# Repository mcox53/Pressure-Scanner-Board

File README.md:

# Pressure-Scanner-Board

Fab To-Do List:
- ~~Add I2C pull up resistors~~
- ~~Revise SPI pin pads to reflect correct configuration~~
- ~~Edit MCU pins once variant files finalized~~
- ~~Complete board BOM~~
- ~~Create changelog~~
- ~~Create PCB footprints and export netlist~~
- ~~Board layout~~
- ~~Design case~~
- ~~Design review~~
- ~~Finalize and release~~
- ~~Order board + parts~~
- ~~Assemble board~~

Test To-Do List:
- ~~Confirm communication with CAN Controller IC~~
- ~~Incorporate basic changes to variant files to support SPI~~
- ~~Test sending and receiving of CAN messages~~
- ~~Confirm communication with Static Pressure Sensor~~
- ~~Confirm communication with Differential Pressure Sensors~~
- ~~Test code to confirm operation of Differential Pressure Sensors.~~
- Test differential pressure sensors with manometer to verify full range of operation. (CC: Charlie Kniffin)
- Weak solder points of SS_0 and SS_3. Fix at shop with reflow station.
- Draft of application code (reading sensors -> preparing data frames -> sending over CAN)
- Prepare Interface Control Document (ICD) and add to AIM CAN configuration
- Finalize application code

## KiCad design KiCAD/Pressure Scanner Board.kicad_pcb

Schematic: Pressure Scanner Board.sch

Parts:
C1, C2: 6.8pF; C_0805
C3, C4, C6, C7, C8: 0.1uF; C_1206
C5: 10uF; C_1206
D1: PRTR5V0U2X; SOT-143
D2: RED; LED_1206
J1: Cortex_Debug; Pin_Header_Straight_2x05_Pitch1.27mm
L1: 470Ohm - FB; L_1806
R1: 10k; R_1210
R2: 330; R_1210
SW1: FSMCTTR
U1: SAMD21G18A-AU; QFP50P900X900X120-48N
Y1: 32.768kHz; CMR200T

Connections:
+3V3: C4.1, C7.1, C8.1, J1.1, L1.1, R1.1, R2.1, U1.17, U1.36, U1.44; also elsewhere on the board
/OSC+: C2.2, U1.1, Y1.1
/OSC-: C1.2, U1.2, Y1.2
GND: C1.1, C2.1, C3.2, C4.2, C5.2, C6.2, C7.2, C8.2, D1.1, D2.1, J1.3, J1.5, SW1.3, SW1.4, U1.5, U1.18, U1.35, U1.42, Y1.3; also elsewhere on the board
MISO_0: U1.21; also elsewhere on the board
MISO_CAN: U1.25; also elsewhere on the board
MOSI_0: U1.19; also elsewhere on the board
MOSI_CAN: U1.27; also elsewhere on the board
unnamed: C3.1, U1.43
unnamed: C5.1, C6.1, L1.2, U1.6
unnamed: D2.2, R2.2
RESETN: J1.10, R1.2, SW1.1, SW1.2, U1.40
SCLK_0: U1.20; also elsewhere on the board
SCLK_CAN: U1.28; also elsewhere on the board
SCL_L: U1.32; also elsewhere on the board
SDA_L: U1.31; also elsewhere on the board
SS_0: U1.13; also elsewhere on the board
SS_1: U1.14; also elsewhere on the board
SS_2: U1.15; also elsewhere on the board
SS_3: U1.16; also elsewhere on the board
SS_CAN: U1.26; also elsewhere on the board
SWCLK: J1.4, U1.45
SWDIO: J1.2, U1.46
USB_D+: D1.3, U1.34; also elsewhere on the board
USB_D-: D1.2, U1.33; also elsewhere on the board
VBUS: D1.4; also elsewhere on the board

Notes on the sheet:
SWD Header
PWR LED
Reset Switch
USB Transient Protection
Pressure Scanner Board - Main
2/8/19
Author: Matthew Cox Organization: University of Connecticut Formula SAE

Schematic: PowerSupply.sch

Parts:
C9, C11: 2.2uF; C_0603
C10: 1.0uF; C_0603
C12, C13: 10uF; C_1206
C14: .1uF; C_0603
F1: 500mA; R_1210
J2: USB_Micro_B; 10104110-0001LF
J3: Conn_01x04; JST_PH_B4B-PH-K_04x2.00mm_Straight
Q1: 3.7A, 30V; SOT-23
R5: 10k; R_0603
U2: AP2112K-3.3; SOT-23-5
U3: LM1117; SOT-223-3_TabPin2

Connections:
+3V3: C11.1, U2.5; also elsewhere on the board
+5V: C10.1, C13.1, C14.1, Q1.2, R5.2, U2.1, U2.3, U3.2; also elsewhere on the board
+BATT: C12.1, J3.1, U3.3
CAN+: J3.3; also elsewhere on the board
CAN-: J3.4; also elsewhere on the board
GND: C9.2, C10.2, C11.2, C12.2, C13.2, C14.2, J2.5, J3.2, Q1.1, R5.1, U2.2, U3.1; also elsewhere on the board
unnamed: C9.1, F1.1, Q1.3
USB_D+: J2.3; also elsewhere on the board
USB_D-: J2.2; also elsewhere on the board
VBUS: F1.2, J2.1; also elsewhere on the board

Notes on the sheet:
VIN: 7-15V
Author: Matthew Cox Organization: University of Connecticut Formula SAE
Pressure Scanner Board - Power Supply
2/8/19
Flying leads terminate to 0.1" pin headers

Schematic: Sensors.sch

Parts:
Q2, Q3: BSS138; SOT-23
R6, R7, R8, R9: 10K; R_1210
U4: HSCDANN015PA2A5
U5, U6, U7, U8, U9, U10, U11, U12: DLHR-L10D-E1BD-C-NAV8

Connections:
+3V3: Q2.1, Q3.1, R6.1, R8.1, U5.2, U7.2, U9.2, U11.2; also elsewhere on the board
+5V: R7.1, R9.1, U4.2; also elsewhere on the board
GND: U4.1, U5.1, U7.1, U9.1, U11.1; also elsewhere on the board
MISO_0: U5.6, U7.6, U9.6, U11.6; also elsewhere on the board
MOSI_0: U5.3, U7.3, U9.3, U11.3; also elsewhere on the board
unnamed: U4.5, U4.6
unnamed: U4.7, U4.8
SCLK_0: U5.4, U7.4, U9.4, U11.4; also elsewhere on the board
SCL_H: Q3.3, R9.2, U4.4
SCL_L: Q3.2, R8.2; also elsewhere on the board
SDA_H: Q2.3, R7.2, U4.3
SDA_L: Q2.2, R6.2; also elsewhere on the board
SS_0: U5.8; also elsewhere on the board
SS_1: U7.8; also elsewhere on the board
SS_2: U9.8; also elsewhere on the board
SS_3: U11.8; also elsewhere on the board

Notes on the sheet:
±10" H2O, 18bit, Differential Pressure Sensors
Optional Expansion Slots
0 - 15 PSIA Pressure Sensor
3.3V to 5V Bi-Directional Level Shift
Pressure Scanner Board - Sensors
2/8/19
Author: Matthew Cox Organization: University of Connecticut Formula SAE
Low voltage signal -> MCU High voltage signal -> Sensor

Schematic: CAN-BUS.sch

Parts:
C15, C17: 0.1uF; C_1206
C16, C18: 22pF; C_0805
D3: ESDA6V1L; SOT-23
J4: Can Header; Pin_Header_Straight_1x02_Pitch2.54mm
R10: 10K; R_1210
R11: 16.9K; R_0805
R12: 120; R_0805
U13: MCP2551; SOIC-8_3.9x4.9mm_Pitch1.27mm
U14: MCP2515; SOIC-18W_7.5x11.6mm_Pitch1.27mm
Y2: 16MHz; 9B-16.000MEEJ-B

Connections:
+3V3: C15.1, R10.1, U14.18; also elsewhere on the board
+5V: C17.1, U13.3; also elsewhere on the board
/CAN Bus/OSC+: C16.2, U14.7, Y2.1
/CAN Bus/OSC-: C18.1, U14.8, Y2.2
CAN+: D3.1, R12.1, U13.7; also elsewhere on the board
CAN-: D3.2, R12.2, U13.6; also elsewhere on the board
GND: C15.2, C16.1, C17.2, C18.2, D3.3, R11.2, U13.2, U14.9; also elsewhere on the board
MISO_CAN: U14.15; also elsewhere on the board
MOSI_CAN: U14.14; also elsewhere on the board
unnamed: R10.2, U14.17
unnamed: R11.1, U13.8
RXCAN: U13.4, U14.2
SCLK_CAN: U14.13; also elsewhere on the board
SS_CAN: U14.16; also elsewhere on the board
TXCAN: U13.1, U14.1

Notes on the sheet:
Author: Matthew Cox Organization: University of Connecticut Formula SAE
Pressure Scanner Board - CAN Bus Interface
2/8/19
CAN Controller + Transceiver
Optional 120 Ohm Termination Resistor
Transient Voltage Protection
Pin Headers -> Binder Series 709

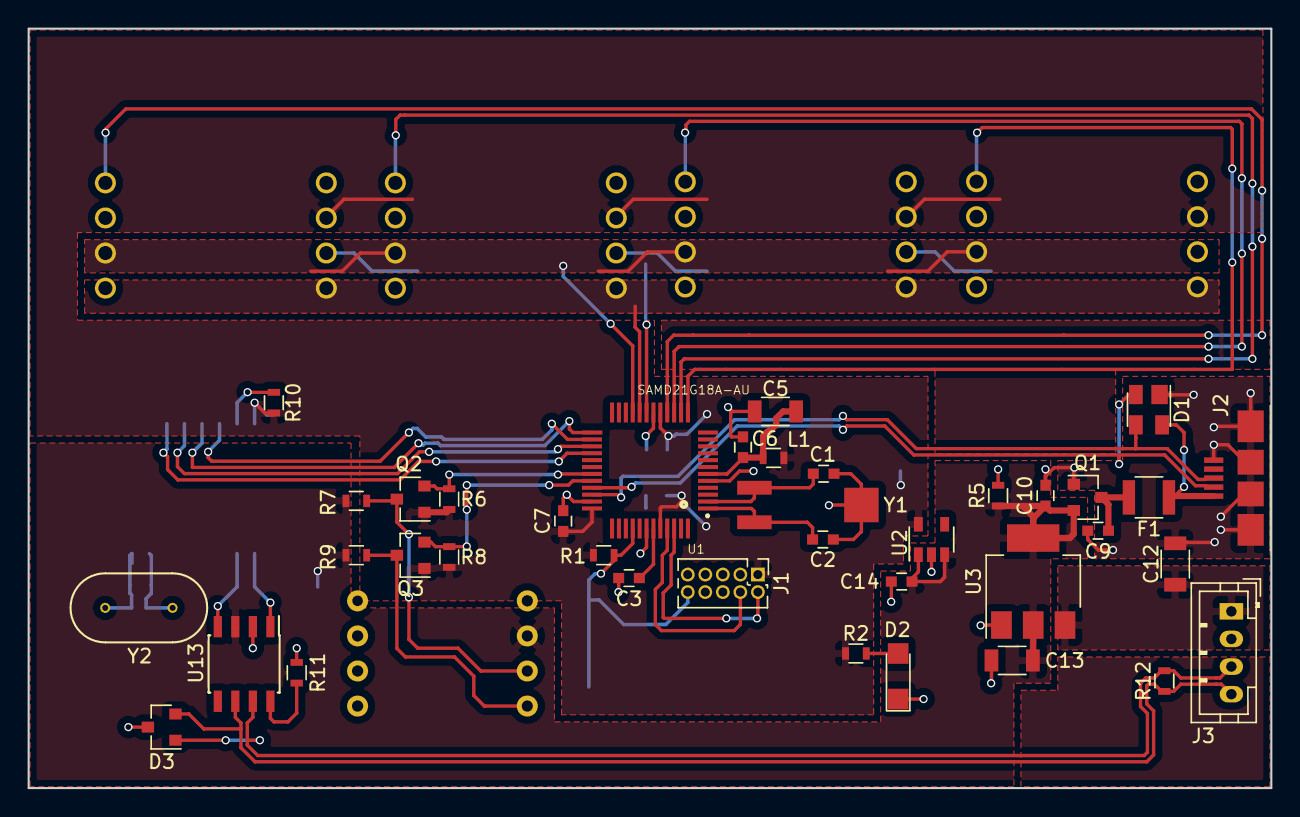
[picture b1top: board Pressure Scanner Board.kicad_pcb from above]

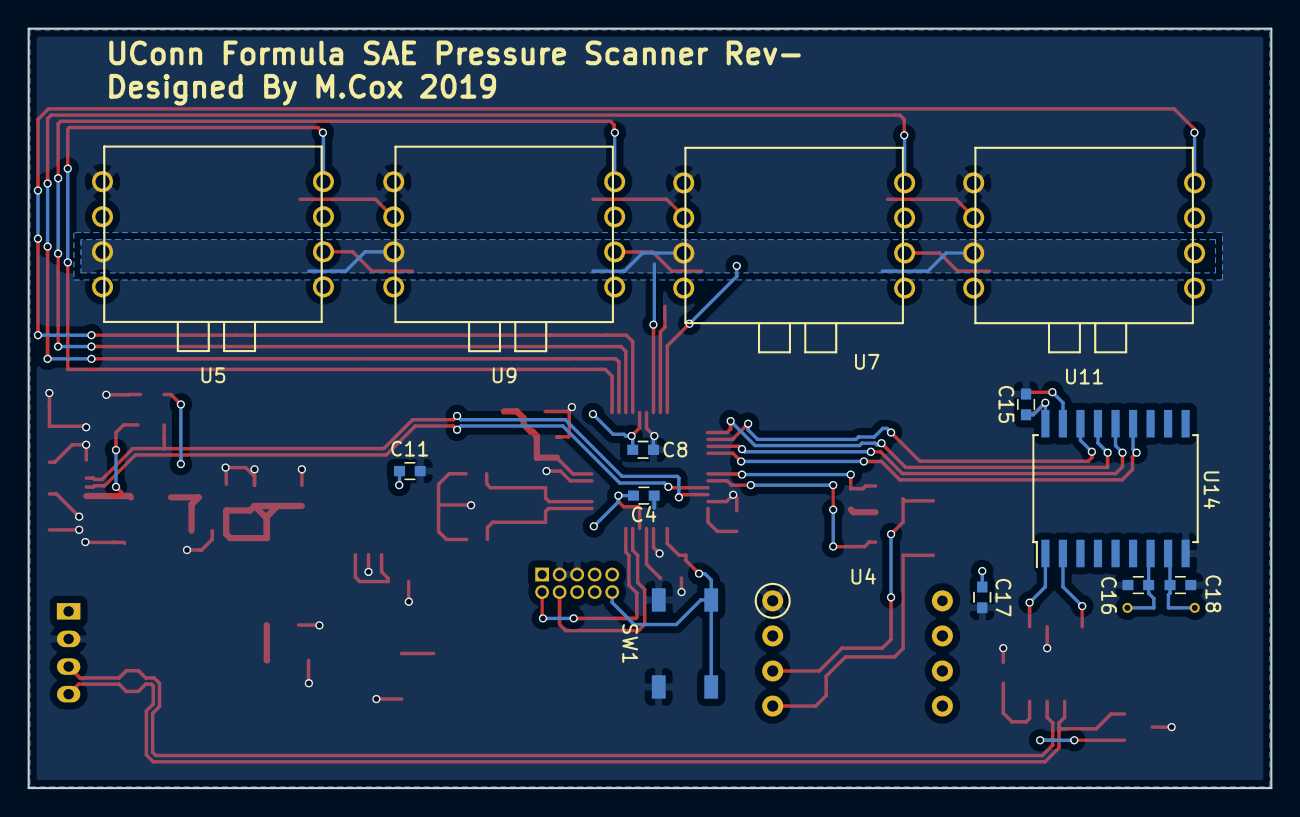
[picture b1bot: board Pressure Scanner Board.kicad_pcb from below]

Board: 2 copper layers, 90.0 x 55.0 mm, 52 parts (14 on the bottom side), 41 nets.

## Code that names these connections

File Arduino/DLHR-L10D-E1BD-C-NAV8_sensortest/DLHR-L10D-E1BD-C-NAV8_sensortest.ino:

/*
 * Author: M. Cox
 * Date: 1/3/19
 * Updated: 10/20/19
 * Description: Testing operation of DLHR-L10D-E1BD-C-NAV8
 * differential pressure sensor on production board
 * Status: Working!
 */
#include <SPI.h>
#include "wiring_private.h"

// Sensor Constants
#define startSingleRead 0xAA
#define startAvg2       0xAC
#define startAvg4       0xAD
#define startAvg8       0xAE
#define startAvg16      0xAF

#define SensorReadByte  0xF0      // This must be followed by 6 bytes of 0x00, done in function
#define SensorStatus    0xF0      // Send only this one byte for status

/* 
 *  Define a new SPI module on SERCOM4
 *  Digital Pin 23 / PB10 / SERCOM4, PAD2 -> MOSI
 *  Digital Pin 24 / PB11 / SERCOM4, PAD3 -> SCK
 *  Digital Pin 22 / PA12 / SERCOM4, PAD0 -> MISO
 *  SPI_PAD_2_SCK_3 indicates MOSI is on PAD2 and SCK on PAD3
 *  SERCOM_RX_PAD_2 indicates MISO is on PAD 2
 *  These pins are already set to PIO_SERCOM_ALT by default for this board
 *  No pinPeripheral() function calls are necessary
 */

SPIClass PressureSPI(&sercom4, 22, 24, 23, SPI_PAD_2_SCK_3, SERCOM_RX_PAD_0);

SPISettings Standard(1000000, MSBFIRST, SPI_MODE0);

const int SS_0 = 4;
const int SS_1 = 3;
const int SS_2 = 1;
const int SS_3 = 0;

// Changed to true (1) when measurement complete
bool measurementStatus = 0;
byte chipStatus;
uint32_t pressureReading;

void setup() {
  SerialUSB.begin(115200);
  while(!SerialUSB);

   // initalize the chip select pins:
  pinMode(SS_0, OUTPUT);
  pinMode(SS_1, OUTPUT);
  pinMode(SS_2, OUTPUT);
  pinMode(SS_3, OUTPUT);
  
  // start the SPI library:
  PressureSPI.begin();

  pinPeripheral(22, PIO_SERCOM_ALT);
  pinPeripheral(23, PIO_SERCOM_ALT);
  pinPeripheral(24, PIO_SERCOM_ALT);
  pinPeripheral(0, PIO_DIGITAL);
  pinPeripheral(1, PIO_DIGITAL);

  digitalWrite(SS_0, HIGH);
  digitalWrite(SS_1, HIGH);
  digitalWrite(SS_2, HIGH);
  digitalWrite(SS_3, HIGH);  
}

void loop() {

  digitalWrite(SS_1, LOW);
  digitalWrite(SS_1, HIGH);

  sendMeasurecmd(startAvg16, SS_1);

  // Continuously read status byte until sensor processing complete
  // This will most likely be a timed polling in the future
  while(measurementStatus == 0){
    chipStatus = readStatus(SS_1);
    byte chipTest = (chipStatus >> 5) & 0b001;
    if(chipTest == 0){
      measurementStatus = 1; 
    }
    delay(1000);
  }
  
  pressureReading = readMeasurement(SS_1);
  measurementStatus = 0;
  
  SerialUSB.println("Pressure (in H20): ");
  // Shift by 8 to see what the 16 bit version would look like 
  SerialUSB.println(pressureReading >> 8);
}

void sendMeasurecmd(byte command, const int chipSelectPin) {

  // Initiate a SPI Transaction
  PressureSPI.beginTransaction(Standard);
  
  // Lower SS pin
  digitalWrite(chipSelectPin, LOW);

  // Measurement commands are a single byte followed by 2 dummy bytes
  PressureSPI.transfer(command); 
  PressureSPI.transfer(0x00);
  PressureSPI.transfer(0x00);

  // Raise SS pin
  digitalWrite(chipSelectPin, HIGH);

  // Complete SPI Transaction
  PressureSPI.endTransaction();
}

uint32_t readMeasurement(const int chipSelectPin){

  uint8_t readByte;
  uint32_t pressure;

  // Initiate a SPI Transaction
  PressureSPI.beginTransaction(Standard);
  
  // Lower SS pin
  digitalWrite(chipSelectPin, LOW);
  
  // Read in status byte
  readByte = PressureSPI.transfer(SensorReadByte);

  // Read in pressure data bytes
  for(uint8_t i = 3; i > 0; i--){
    readByte = PressureSPI.transfer(0x00);
    pressure |= (readByte << (8 * (i - 1)));
  }

  // Send the other three dummy bytes but don't read back the temperature
  PressureSPI.transfer(0x00);
  PressureSPI.transfer(0x00);
  PressureSPI.transfer(0x00);
  
  // Raise SS pin
  digitalWrite(chipSelectPin, HIGH);

  // Complete SPI Transaction
  PressureSPI.endTransaction();
  
  return pressure;
}

byte readStatus(const int chipSelectPin){

  // Initiate a SPI Transaction
  PressureSPI.beginTransaction(Standard);

  // Lower SS pin
  digitalWrite(chipSelectPin, LOW);

  // Send status byte command
  //PressureSPI.transfer(SensorStatus);

  // Send dummy byte to read received byte
  byte statusByte = PressureSPI.transfer(SensorStatus);
  
  // Raise SS pin
  digitalWrite(chipSelectPin, HIGH);

  // Complete SPI Transaction
  PressureSPI.endTransaction();

  return statusByte;
}

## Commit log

2018-11-03 Sorting project files
2018-11-03 Import Libraries from UCONNFSAE/DashboardPCB
2018-12-31 Create HSCDANN015PA2A5_Pressure_Sensor_Test
2018-12-31 Create placeholder
2019-01-03 Static Pressure Sensor test code
2019-01-03 Associated datasheet files
2019-02-07 Sketch to test and verify working SPI commands for sensor
2019-02-07 Sorting files
2019-02-07 Update sensor functions to use proper SPI sequence and settings
2019-02-08 Imported SAMD21 IP, made differential pressure sensor symbol
2019-02-12 Fixed differential pressure sensor pinout
2019-02-12 Created static pressure sensor schematic symbol
2019-02-12 Pinned pressure sensors and added 3.3V - 5V level shifter
2019-02-12 Import libraries to be reused from SAMD21-Dev-Board
2019-02-12 Place power supply from SAMD21-Dev-Board
2019-02-13 Can Bus related Schematic Symbols (MCP2551, MCP2515, CESD5V0AP)
2019-02-13 Added CAN Bus Sheet
2019-02-14 Generic USB Micro B Schematic Symbol
2019-02-14 Add to do list in README
2019-02-14 Schematic Rev 0
2019-02-20 Made pressure sensor footprints
2019-02-20 Associated sensor footprints with parts
2019-03-12 Added footprints for all components and created BOM
2019-03-17 Corrected schematic error, began layout.
2019-03-21 More layout
2019-03-23 Bit more layout, prepping to start routing soon
2019-03-27 Updated CAN Controller Crystal Footprint
2019-03-27 Began routing, added differential pair labels
2019-03-29 Redoing layout
2019-03-30 More Routing
2019-04-16 More route
2019-04-24 Reset the routing
2019-07-12 Swapped most capacitors and resistors to 0603 footprint
2019-07-12 Dropped 4 spare sensors, revising layout.
2019-07-12 Finished layout V0.01
2019-07-12 Export Version 0.01 fab files
2019-07-19 Remove Temp BOM, return to mainline BOM in Drive
2019-07-19 Tidy up soldermask, cleaned up copper pours. Waiting for final packaging design
2019-07-24 Change NPTH Mounting holes and swap to JST PH Series Connector
2019-07-24 Production 1 Fabrication Files
2019-07-24 Group fab outputs for Production run 1
2019-07-26 Exported fab files in proper format for fab house
2019-10-06 Can bus confirmed operational on Rev- Production 1 Board
2019-10-06 Update remaining board tasks
2019-10-06 Update Project to KiCAD 5; Status: REV-, Production 1
2019-10-11 Testing production board for functionality
2019-10-20 Working and tested copy of code to read differential pressure sensors
2019-10-21 Update to-do list
2019-11-02 Draft of application code + test application for all 4 sensors
